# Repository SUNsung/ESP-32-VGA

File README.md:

# ESP-32-VGA
SMD circuit implementation for connecting VGA14Bit specified in https://github.com/bitluni/ESP32Lib  D-SUB dad, calculated to insert into the monitor directly.

Input power from 5V to 9V. 

There is a power indicator, two programmable indicators, hanging on the 25 and 26 pins. 

Control of temperature stabilizer and common on thermistors is untied. VP output is responsible for the stabilizer, VN for overall temperature control.

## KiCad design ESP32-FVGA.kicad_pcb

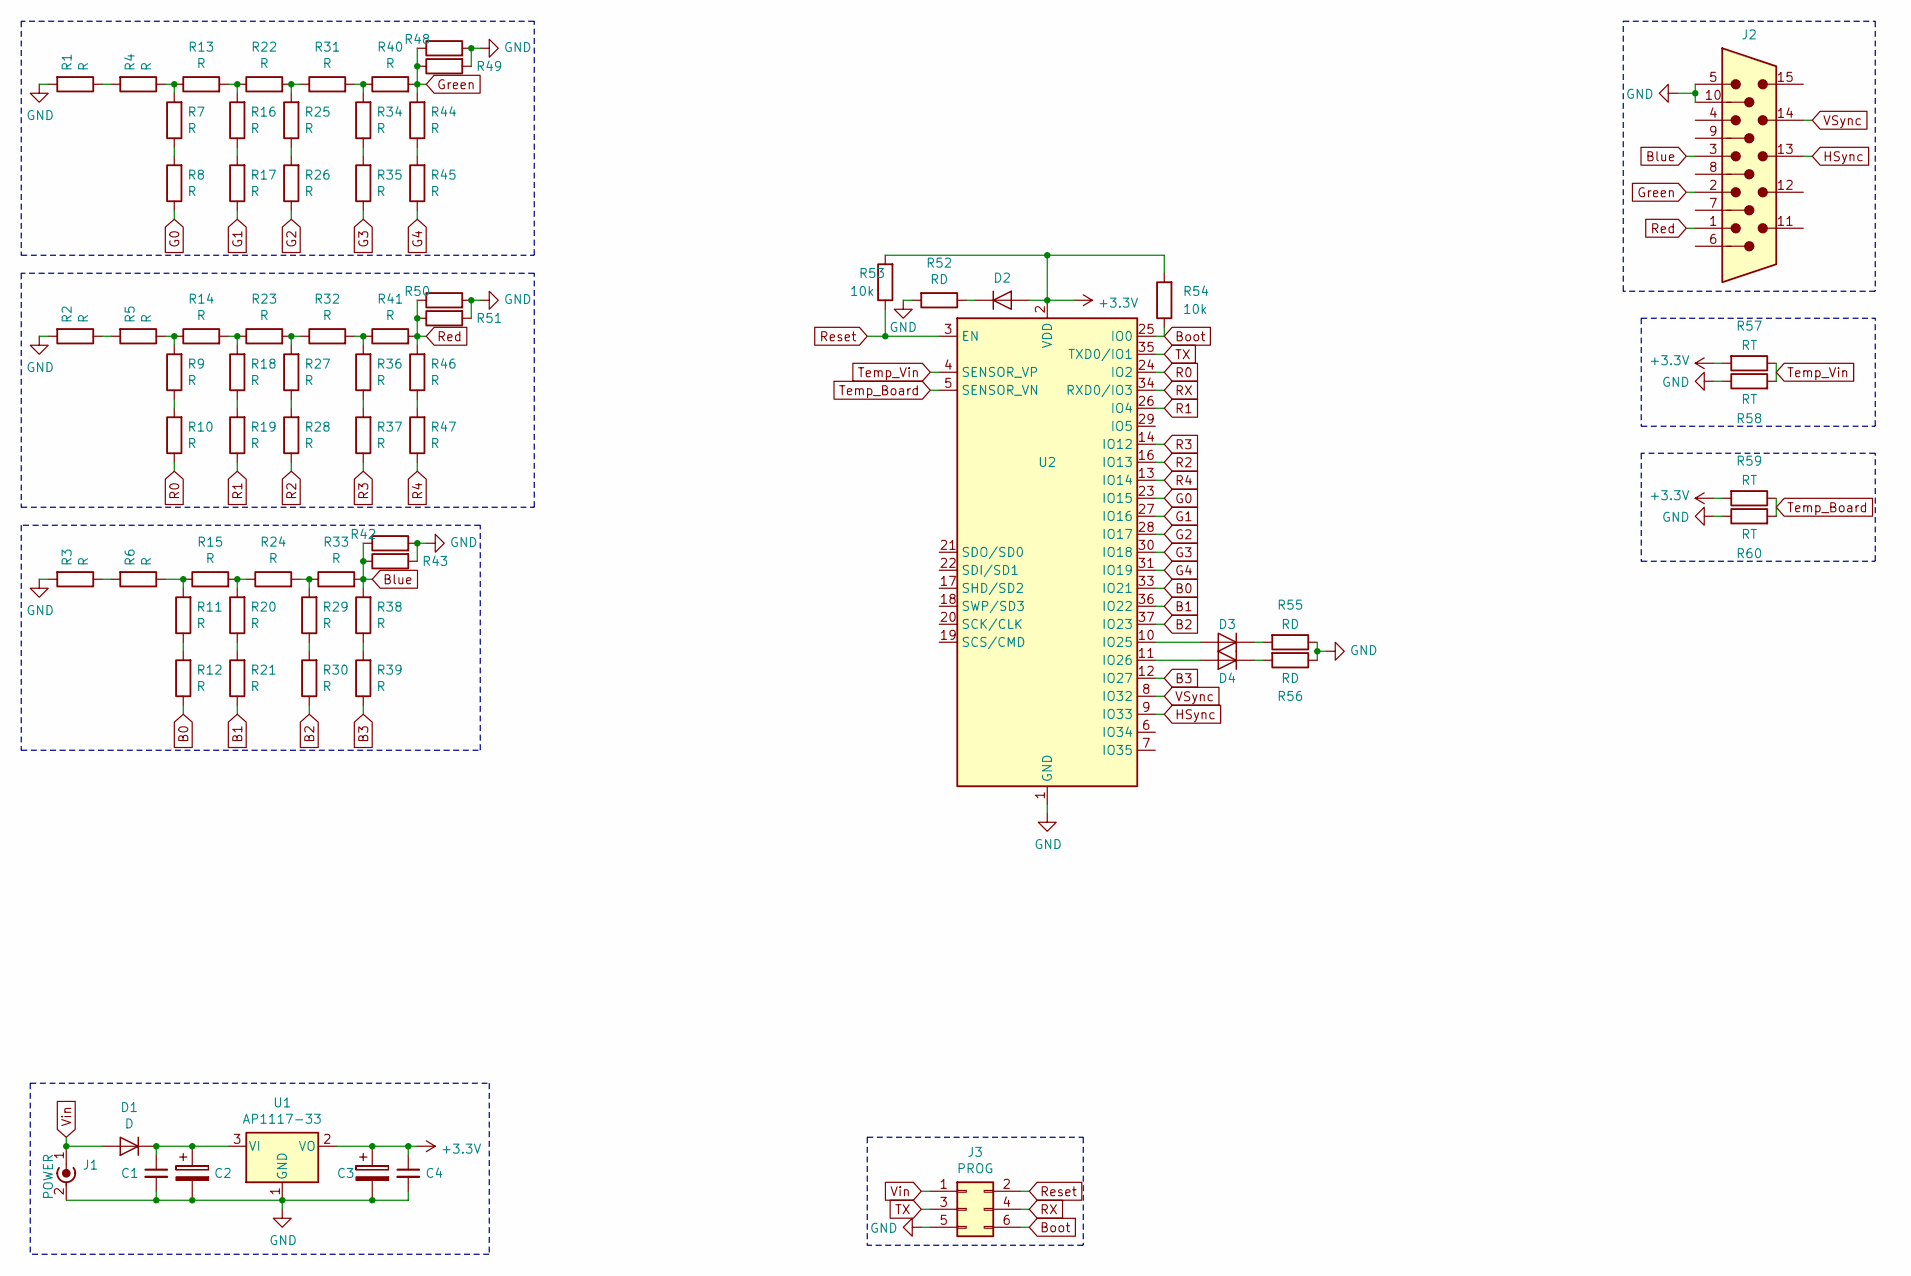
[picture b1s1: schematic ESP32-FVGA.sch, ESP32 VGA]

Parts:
C1, C4: C_Small; C_0805_2012Metric
C2, C3: CP; C_Elec_4x5.8
D1: D; D_SMA
D2, D3, D4: D; D_0805_2012Metric
J1: POWER; BarrelJack_Horizontal
J2: VGA; DSUB-15-HD_Male_Horizontal_P2.29x1.98mm_EdgePinOffset8.35mm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
J3: PROG; IDC-Header_2x03_P2.54mm_Horizontal
R1, R2, R3, R4, R5, R6, R7, R8, R9, R10, R11, R12, R13, R14, R15, R16, R17, R18, R19, R20, R21, R22, R23, R24, R25, R26, R27, R28, R29, R30, R31, R32, R33, R34, R35, R36, R37, R38, R39, R40, R41, R42, R43, R44, R45, R46, R47, R48, R49, R50, R51: R; R_0805_2012Metric
R52, R55, R56: RD; R_0805_2012Metric
R53, R54: 10k; R_0805_2012Metric
R57, R58, R59, R60: RT; R_0805_2012Metric
U1: AP1117-33; SOT-223-3_TabPin2
U2: ESP32-WROOM-32D; ESP32-WROOM-32U

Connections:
+3V3: C3.1, C4.1, D2.2 (A), R53.2, R54.2, R57.2, R59.2, U1.2 (VO), U2.2 (VDD)
B0: R12.1, U2.33 (IO21)
B1: R21.1, U2.36 (IO22)
B2: R30.1, U2.37 (IO23)
B3: R39.1, U2.12 (IO27)
Blue: J2.3, R33.2, R38.2, R42.1, R43.1
Boot: J3.6, R54.1, U2.25 (IO0)
G0: R8.1, U2.23 (IO15)
G1: R17.1, U2.27 (IO16)
G2: R26.1, U2.28 (IO17)
G3: R35.1, U2.30 (IO18)
G4: R45.1, U2.31 (IO19)
GND: C1.2, C2.2, C3.2, C4.2, J1.2 (Ext), J2.5, J2.10, J3.5, R1.2, R2.2, R3.2, R42.2, R43.2, R48.2, R49.2, R50.2, R51.2, R52.2, R55.1, R56.1, R58.1, R60.1, U1.1 (GND), U2.1 (GND), U2.15 (GND), U2.38 (GND), U2.39
Green: J2.2, R40.2, R44.2, R48.1, R49.1
HSync: J2.13, U2.9 (IO33)
unnamed: C1.1, C2.1, D1.1 (K), U1.3 (VI)
unnamed: D2.1 (K), R52.1
unnamed: D3.1 (K), R55.2
unnamed: D3.2 (A), U2.10 (IO25)
unnamed: D4.1 (K), R56.2
unnamed: D4.2 (A), U2.11 (IO26)
unnamed: R1.1, R4.2
unnamed: R2.1, R5.2
unnamed: R3.1, R6.2
unnamed: R7.1, R8.2
unnamed: R9.1, R10.2
unnamed: R11.1, R12.2
unnamed: R6.1, R11.2, R15.1
unnamed: R4.1, R7.2, R13.1
unnamed: R13.2, R16.2, R22.1
unnamed: R5.1, R9.2, R14.1
unnamed: R14.2, R18.2, R23.1
unnamed: R15.2, R20.2, R24.1
unnamed: R16.1, R17.2
unnamed: R18.1, R19.2
unnamed: R20.1, R21.2
unnamed: R22.2, R25.2, R31.1
unnamed: R23.2, R27.2, R32.1
unnamed: R24.2, R29.2, R33.1
unnamed: R25.1, R26.2
unnamed: R27.1, R28.2
unnamed: R29.1, R30.2
unnamed: R31.2, R34.2, R40.1
unnamed: R32.2, R36.2, R41.1
unnamed: R34.1, R35.2
unnamed: R36.1, R37.2
unnamed: R38.1, R39.2
unnamed: R44.1, R45.2
unnamed: R46.1, R47.2
R0: R10.1, U2.24 (IO2)
R1: R19.1, U2.26 (IO4)
R2: R28.1, U2.16 (IO13)
R3: R37.1, U2.14 (IO12)
R4: R47.1, U2.13 (IO14)
RX: J3.4, U2.34 (RXD0/IO3)
Red: J2.1, R41.2, R46.2, R50.1, R51.1
Reset: J3.2, R53.1, U2.3 (EN)
TX: J3.3, U2.35 (TXD0/IO1)
Temp_Board: R59.1, R60.2, U2.5 (SENSOR_VN)
Temp_Vin: R57.1, R58.2, U2.4 (SENSOR_VP)
VSync: J2.14, U2.8 (IO32)
Vin: D1.2 (A), J1.1 (In), J3.1

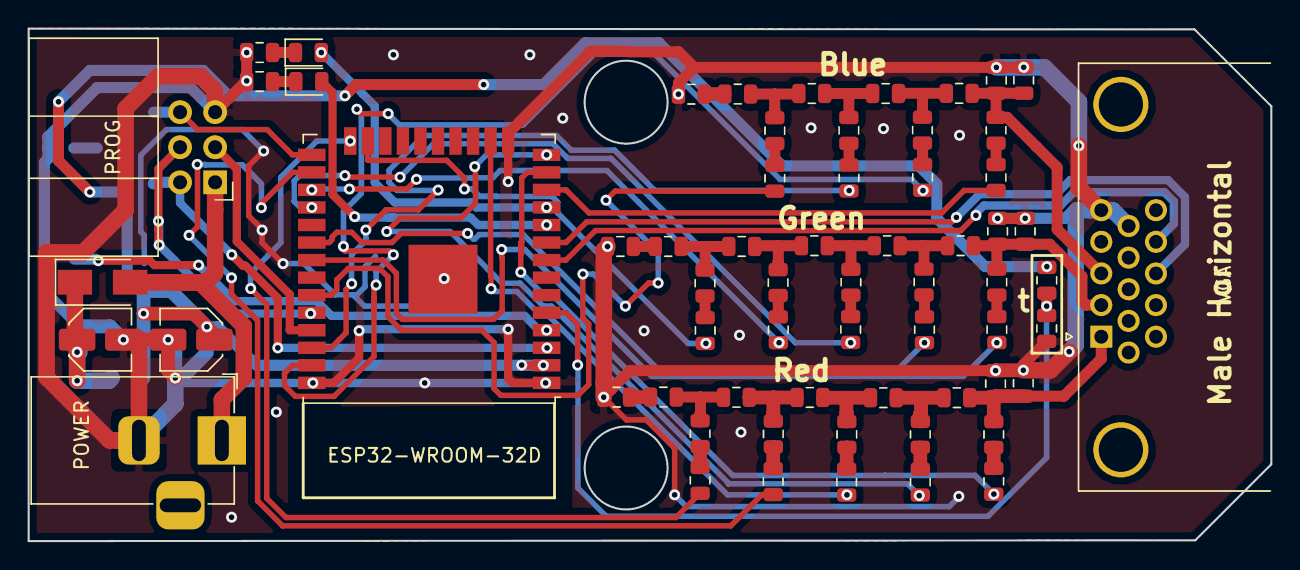
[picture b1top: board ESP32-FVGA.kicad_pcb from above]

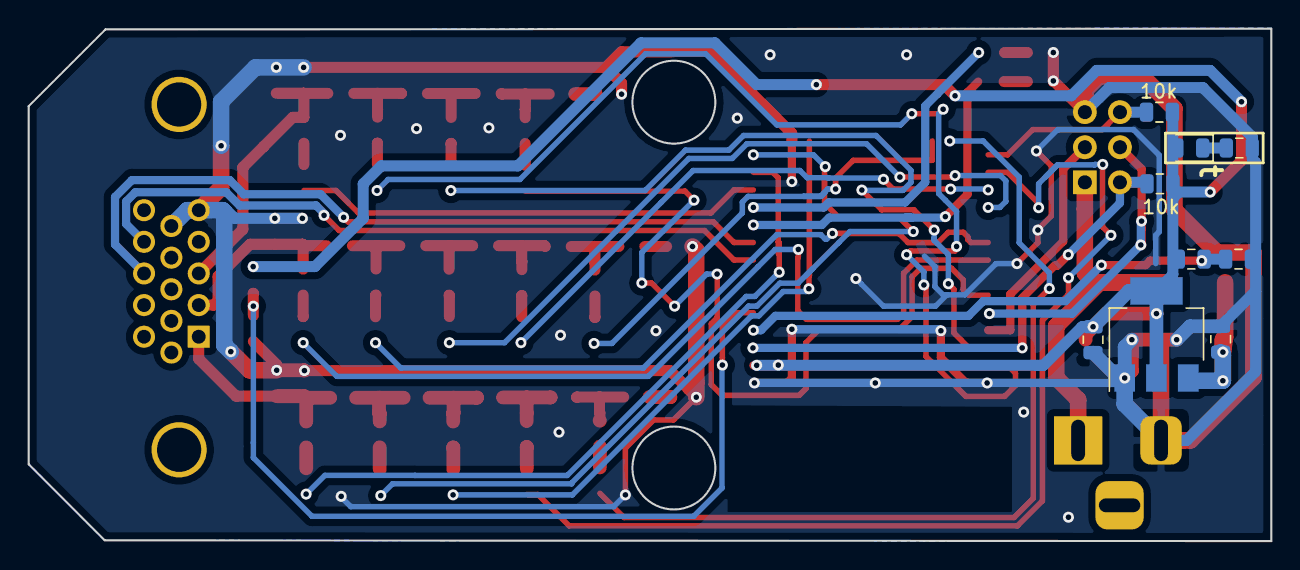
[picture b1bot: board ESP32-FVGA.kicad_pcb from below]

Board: 2 copper layers, 90.0 x 37.1 mm, 73 parts (9 on the bottom side), 62 nets.

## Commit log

2019-04-17 3D
    3d models
2019-04-17 rend img
